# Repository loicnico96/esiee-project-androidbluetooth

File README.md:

# esiee-project-androidbluetooth

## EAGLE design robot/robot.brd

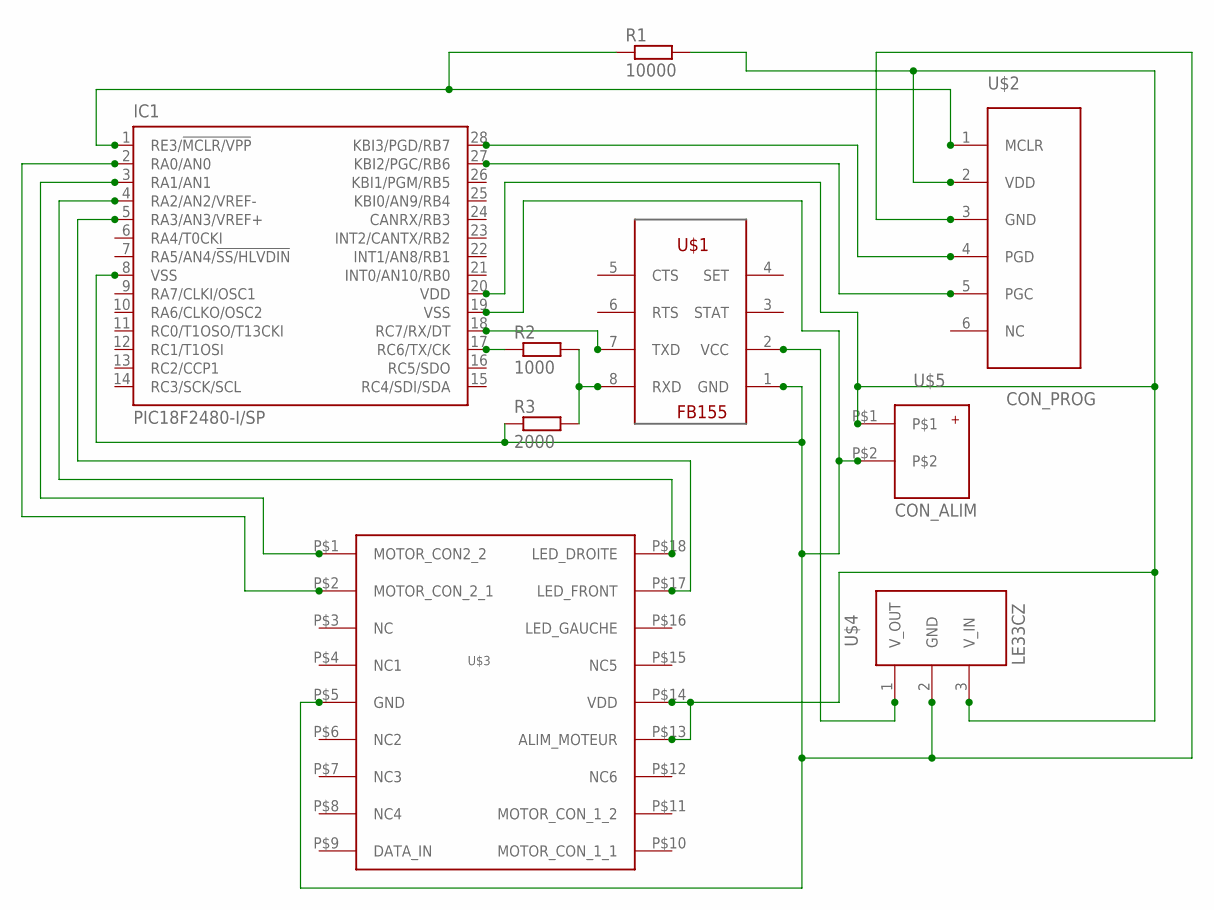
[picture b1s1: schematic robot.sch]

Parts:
IC1: PIC18F2480-I/SP; DIL28-3
R1: 10000; 0207/7
R2: 1000; 0207/7
R3: 2000; 0207/7
U$1: FB155; DIL8L
U$2: CON_PROG
U$3: ROBOT; CON_ROBOT
U$4: LE33CZ; T092
U$5: CON_ALIM

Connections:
unnamed: IC1.2 (RA0/AN0), U$3.P$2 (MOTOR_CON_2_1)
unnamed: IC1.3 (RA1/AN1), U$3.P$1 (MOTOR_CON2_2)
unnamed: IC1.4 (RA2/AN2/VREF-), U$3.P$18 (LED_DROITE)
unnamed: IC1.5 (RA3/AN3/VREF+), U$3.P$17 (LED_FRONT)
unnamed: IC1.28 (KBI3/PGD/RB7), U$2.4 (PGD)
unnamed: IC1.27 (KBI2/PGC/RB6), U$2.5 (PGC)
unnamed: IC1.17 (RC6/TX/CK), R2.1
unnamed: R2.2, R3.2, U$1.8 (RXD)
unnamed: U$1.2 (VCC), U$4.1 (V_OUT)
unnamed: IC1.1 (RE3/!MCLR/VPP), R1.1, U$2.1 (MCLR)
unnamed: IC1.8 (VSS), IC1.19 (VSS), R3.1, U$1.1 (GND), U$2.3 (GND), U$3.P$5 (GND), U$4.2 (GND), U$5.P$2
unnamed: IC1.18 (RC7/RX/DT), U$1.7 (TXD)
unnamed: IC1.20 (VDD), R1.2, U$2.2 (VDD), U$3.P$13 (ALIM_MOTEUR), U$3.P$14 (VDD), U$4.3 (V_IN), U$5.P$1

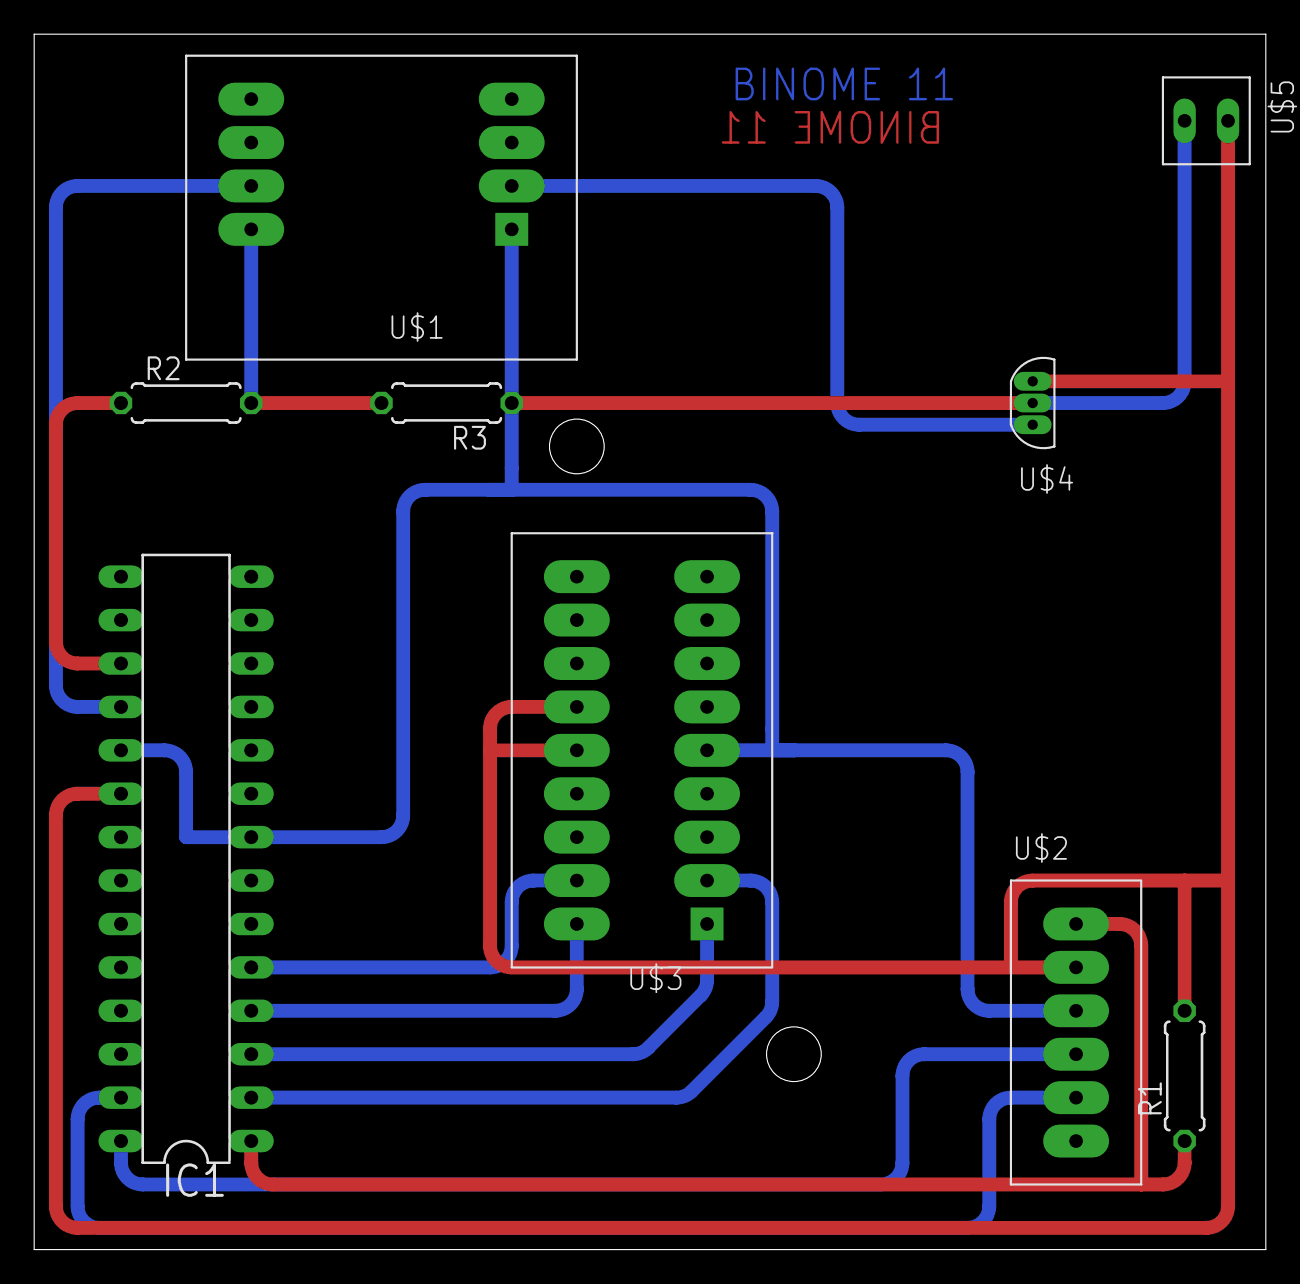
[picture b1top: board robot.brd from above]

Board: 2 copper layers, 72.1 x 71.1 mm, 9 parts (0 on the bottom side), 13 nets.

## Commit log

2018-06-13 initial commit - robot code
